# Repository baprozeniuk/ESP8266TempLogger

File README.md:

# ESP8266 Temperature Logger
Designed and tested on a Lolin NodeMCU V3. Sends temperature over UDP from a DS18B20 connected to an ESP8266 microcontroller.

# Data Format
Temperature is sent in a single UDP packet with a payload of 12 bytes to a configurable host and port. 
First 6 bytes contain the MAC address of the ESP8266 as a unique identifier
Second 2 bytes contain a 16 bit unsigned integer to identify the sensor. Multiple Sensors are not yet supported, so this value is always 0x0000
Final 4 bytes contain a 32 bit floating point value from the sensor in Celsius 

# Configuration
The WiFi network configured in the ESP8266 EEPROM will be used by default. If you have previously programmed the microcontroller, the reset config switch should be activated on first boot. If you have previously programmed a WiFi network and do not reset the controller the host and port will be improperly configured ad the program is likely to crash, or send no data.

The configuration mode is triggered either by closing the reset circuit, or if a wifi connection fails. 

Once in configuration mode, a WiFi network named "ESP8266" will be created. This network will direct you to a captive portal at 192.168.4.1. Enter your WiFi network configuration, server name and port. Make sure that the reset circuit is open before saving otherwise it will re-enter configuration mode upon reboot. 

# Consuming Data
An example Python script is included. 

The script includes alerting via email and amazon SNS, logging to console, database and csv file.

Another example server is located at https://github.com/andrewmacheret/temperature-sensor-server

# Build Dependencies 
 * WiFi Manager: https://github.com/tzapu/WiFiManager
 * OneWire: https://www.pjrc.com/teensy/td_libs_OneWire.html
 * ESP8266 Libraries from: https://github.com/esp8266/Arduino
 * Maxim/Dallas Temperature Library: https://github.com/milesburton/Arduino-Temperature-Control-Library

# Parts Required
 * ESP8266 (ESP12E or ESP12F should work). WEMOS boards also work.
 * DS18B20 1-Wire temperature Sensor
 * 2x 4.7kΩ resistors
 * 1 switch of some type. Needs to be able to be closed for 1 durration of the program
 * 3.3V power supply, or use the voltage regulator configuration described in the wiring diagram and cad files
 
 # Wiring Diagram

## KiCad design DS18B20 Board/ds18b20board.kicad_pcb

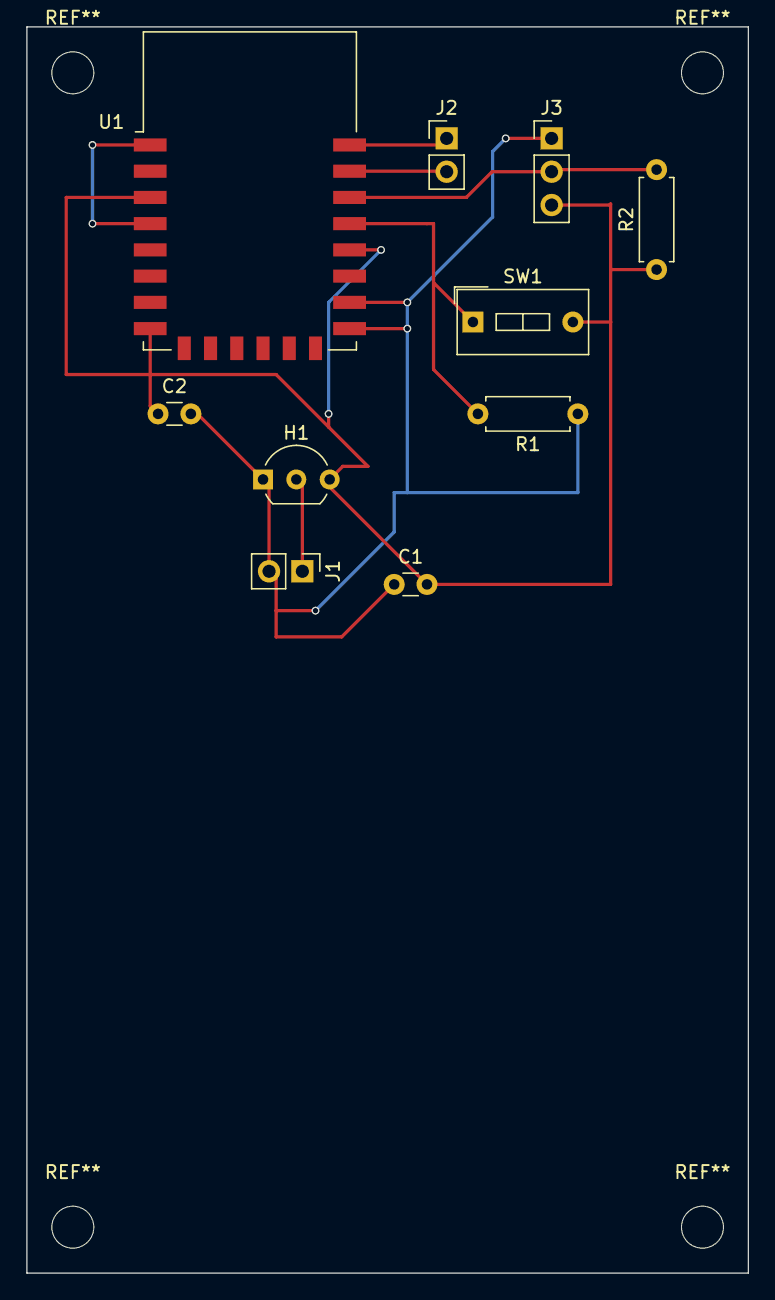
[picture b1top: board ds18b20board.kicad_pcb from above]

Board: 2 copper layers, 55.0 x 95.0 mm, 10 parts (0 on the bottom side), 8 nets.

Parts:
C1: 0.1uF; C_Disc_D3.0mm_W1.6mm_P2.50mm
C2: 100nF; C_Disc_D3.0mm_W1.6mm_P2.50mm
H1: HT7333; TO-92_Inline_Wide
J1: BATT; Pin_Header_Straight_1x02_Pitch2.54mm
J2: Conn_01x02; Pin_Header_Straight_1x02_Pitch2.54mm
J3: CONN_DS18B20; Pin_Header_Straight_1x03_Pitch2.54mm
R1, R2: 4.7k; R_Axial_DIN0207_L6.3mm_D2.5mm_P7.62mm_Horizontal
SW1: SW_DIP_x01; SW_DIP_x1_W7.62mm_Slide
U1: ESP-12E

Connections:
/CONF: R1.2, SW1.1, U1.19
/DS: U1.1, U1.4
/DS18B20: J3.2, R2.2, U1.20
/GND: C1.1, C2.2, H1.1, J1.2, J3.1, R1.1, U1.15, U1.16
/RX: J2.2, U1.21
/TX: J2.1, U1.22
/VCC: C1.2, C2.1, H1.3, J3.3, R2.1, SW1.2, U1.3, U1.8, U1.18
/VIN: H1.2, J1.1

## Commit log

2017-10-02 Add files via upload
    Testing server in python 2.7
2017-10-02 renamed arduino file and increased temperature sensor ID lenght from 8 bits to 16 bits.
2017-10-02 Re-added in deep sleep, set to 60 seconds
2017-10-02 removed debug code, removed unused commented code, improved comments.
2017-10-06 Changed Wifi Conection to sleep rather than enter config mode upon connection failure. Added timeout for sensor at about 10 seconds.
2018-05-08 arduino code fixes to be consistent with final design, test server updated with alerting (sms and email) and database logging
2018-05-08 removed configured password. made script a bit more proper, with methods and all yo
2018-05-08 actually removed passwords
2018-05-08 added kicad files
2018-05-08 updated wiring diagram
2018-05-08 cleaned up code, added methods for email sms and database and removed from main loop
2018-05-08 added comments
2018-05-12 moved config to external json file
2018-05-12 renamed test.py to collector.py
2018-05-12 fixed type in filename
2018-05-12 added web application for getting results from the DB and setting friendly names for sensors
2018-06-01 added files for new version of the PCB
2018-06-01 added png of schematic
2018-06-01 made png better
